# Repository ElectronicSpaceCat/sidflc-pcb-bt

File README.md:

# sidflc-pcb-bt

The primary pcb has the bluetooth module (where the firmware resides).

KiCad version: 7.0

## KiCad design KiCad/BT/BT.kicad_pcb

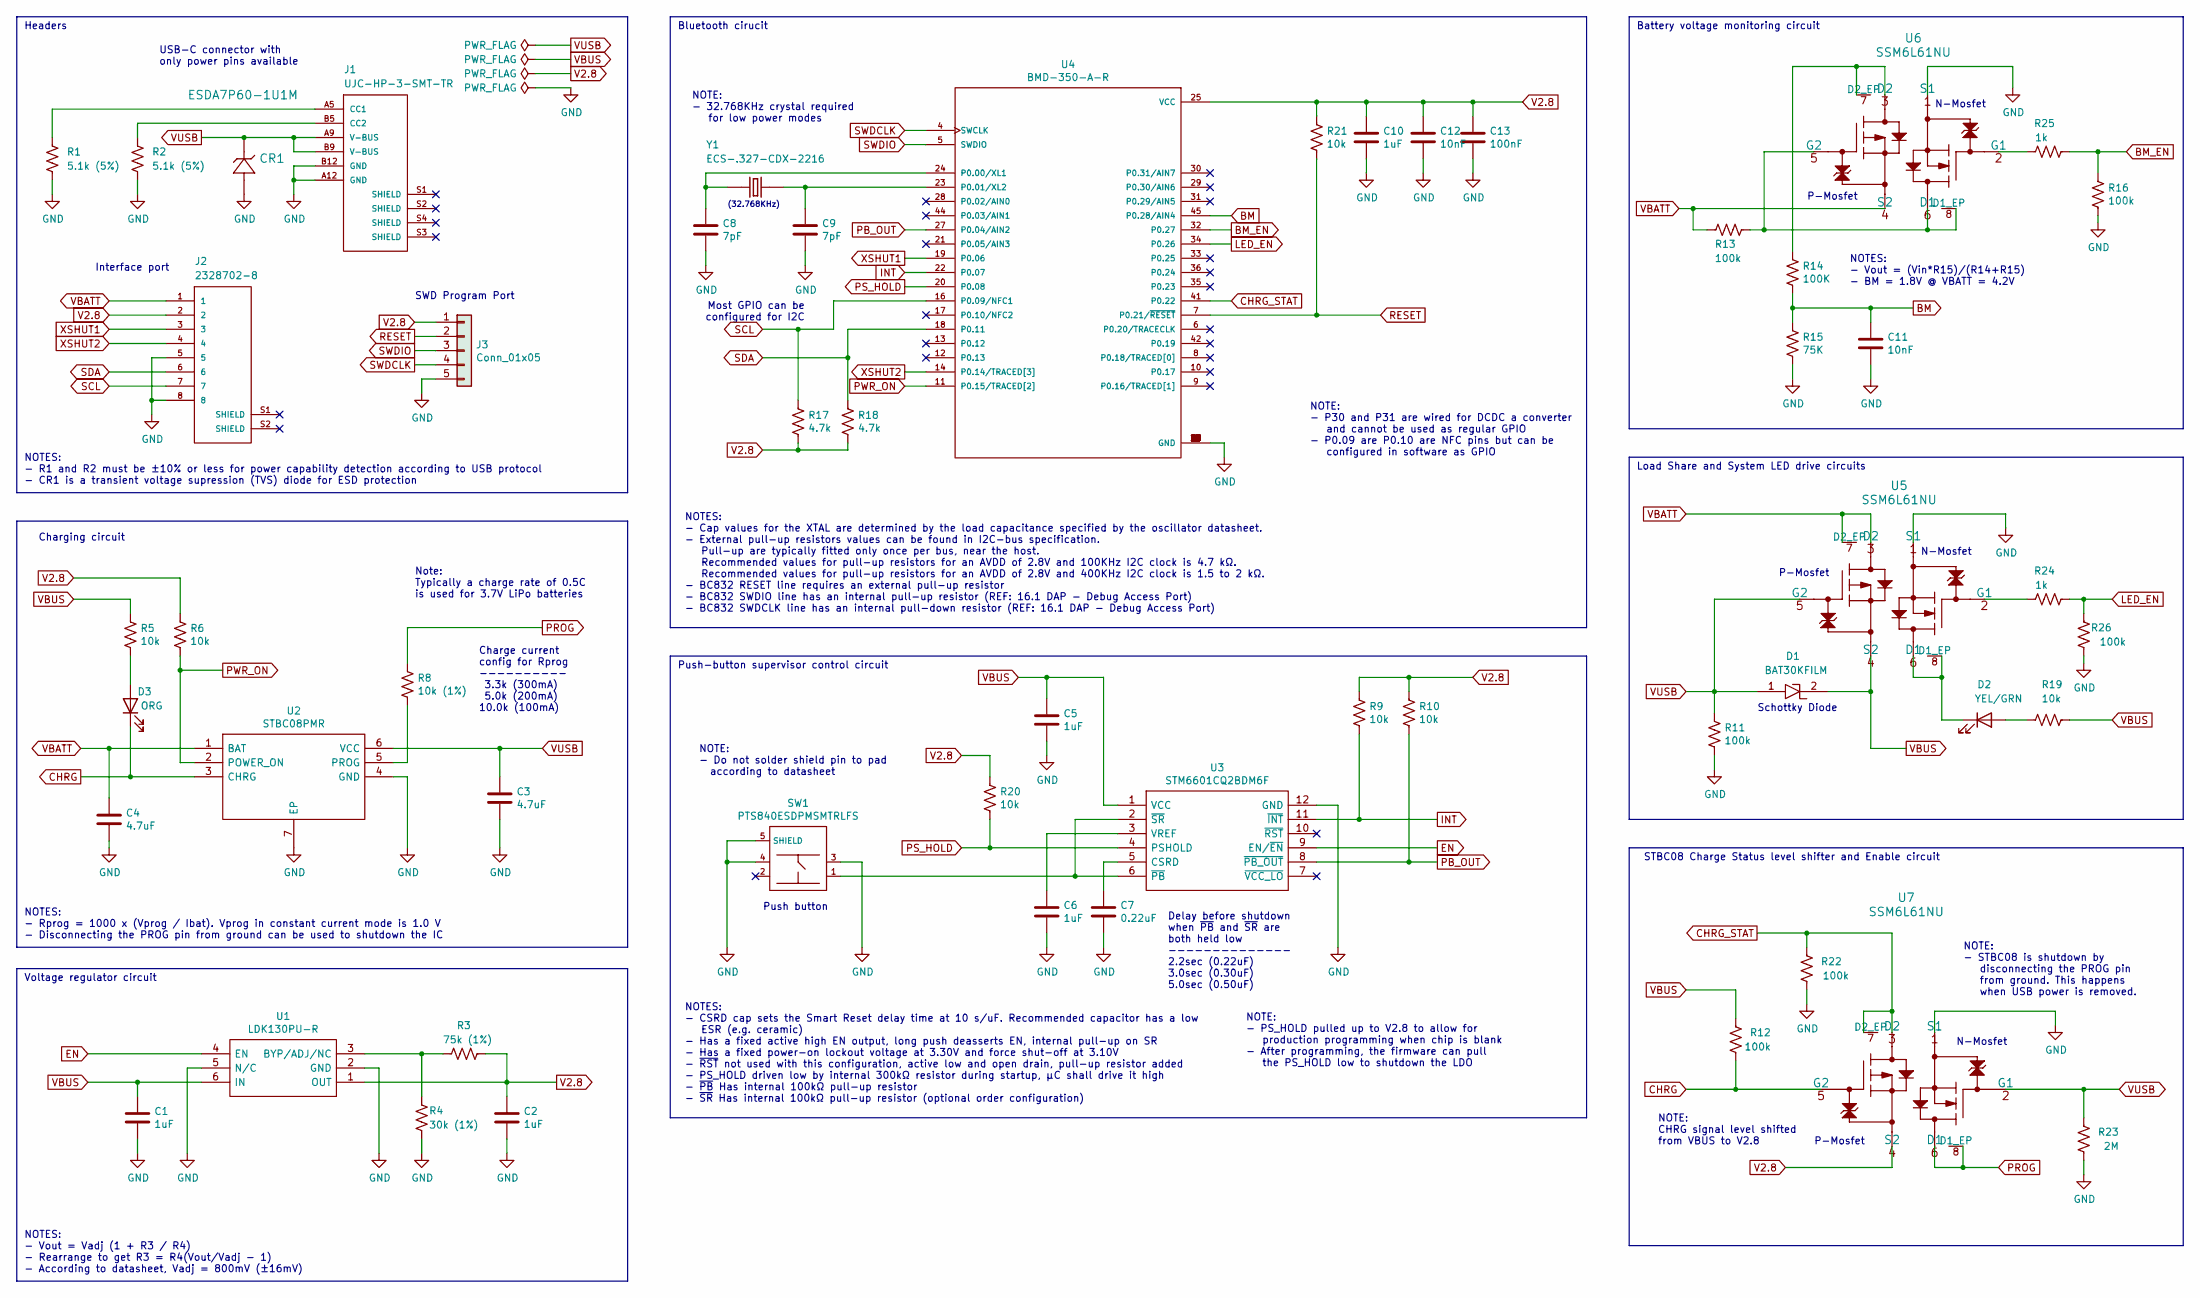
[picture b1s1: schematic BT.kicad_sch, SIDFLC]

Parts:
C1, C2, C5, C6, C10: 1uF; Capacitor_Taiyo_Yuden_0402
C3, C4: 4.7uF; Capacitor_Taiyo_Yuden_0402
C7: 0.22uF; Capacitor_Taiyo_Yuden_0402
C8, C9: 7pF; C_0201_0603Metric
C11, C12: 10nF; Capacitor_Taiyo_Yuden_0402
C13: 100nF; Capacitor_Taiyo_Yuden_0402
CR1: ESDA7P60-1U1M; ESDA7P601U1M
D1: BAT30KFILM; Manufacturer_Part_Number BAT30KFILM; Mouser Part Number 511-BAT30KFILM
D2: YEL/GRN; LED_QBLP595
D3: ORG; LED_QBLP595
J1: UJC-HP-3-SMT-TR; CUI_UJC-HP-3-SMT-TR; PARTREV 1.0
J2: 2328702-8; TE_2328702-8
J3: Conn_01x05; PinHeader_1x05_P1.00mm_Vertical
R1, R2: 5.1k (5%); Stackpole_Res_0402
R3: 75k (1%); Stackpole_Res_0402
R4: 30k (1%); Stackpole_Res_0402
R5, R6, R9, R10, R19, R20, R21: 10k; Stackpole_Res_0402
R8: 10k (1%); Stackpole_Res_0402
R11, R12, R13, R16, R22, R26: 100k; Stackpole_Res_0402
R14: 100K; Stackpole_Res_0402
R15: 75K; Stackpole_Res_0402
R17, R18: 4.7k; Stackpole_Res_0402
R23: 2M; Stackpole_Res_0402
R24, R25: 1k; Stackpole_Res_0402
SW1: PTS840ESDPMSMTRLFS
U1: LDK130PU-R; QFN40P120X130X45-6N; Manufacturer_Part_Number LDK120PU29R
U2: STBC08PMR; SON95P300X300X100-7N-D; Manufacturer_Part_Number STBC08PMR; Mouser Part Number 511-STBC08PMR
U3: STM6601CQ2BDM6F; STM6601AQ2BDM6F; Manufacturer_Part_Number STM6601CQ2BDM6F; Mouser Part Number 511-STM6601CQ2BDM6F
U4: BMD-350-A-R; XCVR_BMD-350-A-R; PARTREV 2.0
U5, U6, U7: SSM6L61NU; UDFN6
Y1: ECS-.327-CDX-2216; XTAL_ECS-.327-CDX-2216; PARTREV 2016

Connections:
BM: C11.1, R14.2, R15.1, U4.45 (P0.28/AIN4)
BM_EN: R16.1, R25.2, U4.32 (P0.27)
CHRG: D3.1 (K), R12.1, U2.3 (CHRG), U7.5 (G2)
CHRG_STAT: R22.2, U4.41 (P0.22), U7.3 (D2), U7.7 (D2_EP)
EN: U1.4 (EN), U3.9 (EN/~EN)
GND: C1.2, C2.2, C3.2, C4.2, C5.2, C6.2, C7.2, C8.2, C9.2, C10.2, C11.2, C12.2, C13.2, CR1.2, J1.A12 (GND), J1.B12 (GND), J2.5, J2.8, J3.5, R1.2, R2.2, R4.2, R11.2, R15.2, R16.2, R22.1, R23.1, R26.1, SW1.3, SW1.4, SW1.5 (SHIELD), U1.2 (GND), U1.5 (N/C), U2.4 (GND), U2.7 (EP), U3.12 (GND), U4.1 (GND), U4.2 (GND), U4.3 (GND), U4.15 (GND), U4.26 (GND), U4.37 (GND), U4.38 (GND), U4.39 (GND), U4.40 (GND), U4.43 (GND), U4.46 (GND), U4.47 (GND), U5.1 (S1), U6.1 (S1), U7.1 (S1)
INT: R9.2, U3.11 (~INT), U4.22 (P0.07)
LED_EN: R24.2, R26.2, U4.34 (P0.26)
unnamed: D2.2 (A), R19.2
unnamed: D2.1 (K), U5.6 (D1), U5.8 (D1_EP)
unnamed: D3.2 (A), R5.2
unnamed: J1.A5 (CC1), R1.1
unnamed: J1.B5 (CC2), R2.1
unnamed: R3.1, R4.1, U1.3 (BYP/ADJ/NC)
unnamed: R8.2, U2.5 (PROG)
unnamed: C7.1, U3.5 (CSRD)
unnamed: C6.1, U3.3 (VREF)
unnamed: SW1.1, U3.2 (~SR), U3.6 (~PB)
unnamed: C8.1, U4.24 (P0.00/XL1), Y1.1
unnamed: C9.1, U4.23 (P0.01/XL2), Y1.2
unnamed: R24.1, U5.2 (G1)
unnamed: R13.1, U6.5 (G2), U6.6 (D1), U6.8 (D1_EP)
unnamed: R14.1, U6.3 (D2), U6.7 (D2_EP)
unnamed: R25.1, U6.2 (G1)
PB_OUT: R10.2, U3.8 (~PB_OUT), U4.27 (P0.04/AIN2)
PROG: R8.1, U7.6 (D1), U7.8 (D1_EP)
PS_HOLD: R20.2, U3.4 (PSHOLD), U4.20 (P0.08)
PWR_ON: R6.2, U2.2 (POWER_ON), U4.11 (P0.15/TRACED[2])
RESET: J3.2, R21.2, U4.7 (P0.21/~RESET)
SCL: J2.7, R17.1, U4.16 (P0.09/NFC1)
SDA: J2.6, R18.1, U4.18 (P0.11)
SWDCLK: J3.4, U4.4 (SWCLK)
SWDIO: J3.3, U4.5 (SWDIO)
V2.8: C2.1, C10.1, C12.1, C13.1, J2.2, J3.1, R3.2, R6.1, R9.1, R10.1, R17.2, R18.2, R20.1, R21.1, U1.1 (OUT), U4.25 (VCC), U7.4 (S2)
VBATT: C4.1, J2.1, R13.2, U2.1 (BAT), U5.3 (D2), U5.7 (D2_EP), U6.4 (S2)
VBUS: C1.1, C5.1, D1.2, R5.1, R12.2, R19.1, U1.6 (IN), U3.1 (VCC), U5.4 (S2)
VUSB: C3.1, CR1.1, D1.1, J1.A9 (V-BUS), J1.B9 (V-BUS), R11.1, R23.2, U2.6 (VCC), U5.5 (G2), U7.2 (G1)
XSHUT1: J2.3, U4.19 (P0.06)
XSHUT2: J2.4, U4.14 (P0.14/TRACED[3])

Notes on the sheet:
SWD Program Port
Charge current config for Rprog ---------- 3.3k (300mA) 5.0k (200mA) 10.0k (100mA)
Push button
STBC08 Charge Status level shifter and Enable circuit
NOTES: - Cap values for the XTAL are determined by the load capacitance specified by the oscillator datasheet. - External pull-up resistors values can be found in I2C-bus specification. Pull-up are typically fitted only once per bus, near the host. Recommended values for pull-up resistors for an AV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
Headers
NOTE: - PS_HOLD pulled up to V2.8 to allow for production programming when chip is blank - After programming, the firmware can pull the PS_HOLD low to shutdown the LDO
NOTES: - R1 and R2 must be ±10% or less for power capability detection according to USB protocol - CR1 is a transient voltage supression (TVS) diode for ESD protection
N-Mosfet
(32.768KHz)
Voltage regulator circuit
Schottky Diode
NOTES: - Vout = Vadj (1 + R3 / R4) - Rearrange to get R3 = R4(Vout/Vadj - 1) - According to datasheet, Vadj = 800mV (±16mV)
Bluetooth cirucit
Note: Typically a charge rate of 0.5C is used for 3.7V LiPo batteries
NOTE: - Do not solder shield pin to pad according to datasheet
Interface port
Load Share and System LED drive circuits
Battery voltage monitoring circuit
NOTE: CHRG signal level shifted from VBUS to V2.8
NOTES: - Vout = (Vin*R15)/(R14+R15) - BM = 1.8V @ VBATT = 4.2V
Push-button supervisor control circuit
NOTE: - STBC08 is shutdown by disconnecting the PROG pin from ground. This happens when USB power is removed.
NOTE: - 32.768KHz crystal required for low power modes
Most GPIO can be configured for I2C
NOTES: - CSRD cap sets the Smart Reset delay time at 10 s/uF. Recommended capacitor has a low ESR (e.g. ceramic) - Has a fixed active high EN output, long push deasserts EN, internal pull-up on SR - Has a fixed power-on lockout voltage at 3.30V and force shut-off at 3.10V - ~{RST} not used with thi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
P-Mosfet
Charging circuit
Delay before shutdown when ~{PB} and ~{SR} are both held low -------------- 2.2sec (0.22uF) 3.0sec (0.30uF) 5.0sec (0.50uF)
NOTE: - P30 and P31 are wired for DCDC a converter and cannot be used as regular GPIO - P0.09 are P0.10 are NFC pins but can be configured in software as GPIO
NOTES: - Rprog = 1000 x (Vprog / Ibat). Vprog in constant current mode is 1.0 V - Disconnecting the PROG pin from ground can be used to shutdown the IC
USB-C connector with only power pins available

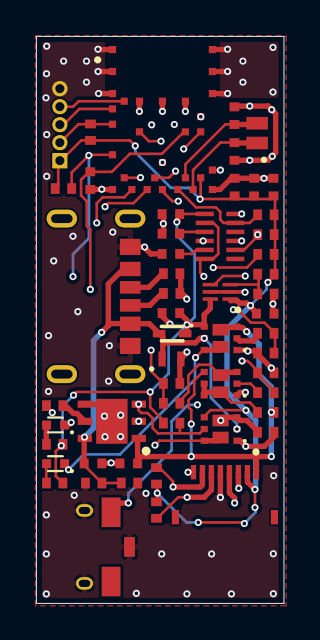
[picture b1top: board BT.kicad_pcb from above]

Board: 4 copper layers, 13.8 x 31.5 mm, 54 parts (0 on the bottom side), 39 nets.

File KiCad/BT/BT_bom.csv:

"#","Reference","Qty","Value","Footprint","DNP"
"1","C1, C2, C5, C6, C10","5","1uF","Capacitor_Taiyo_Yuden_0402:Capacitor_Taiyo_Yuden_0402",""
"2","C3, C4","2","4.7uF","Capacitor_Taiyo_Yuden_0402:Capacitor_Taiyo_Yuden_0402",""
"3","C7","1","0.22uF","Capacitor_Taiyo_Yuden_0402:Capacitor_Taiyo_Yuden_0402",""
"4","C8, C9","2","7pF","Capacitor_SMD:C_0201_0603Metric",""
"5","C11, C12","2","10nF","Capacitor_Taiyo_Yuden_0402:Capacitor_Taiyo_Yuden_0402",""
"6","C13","1","100nF","Capacitor_Taiyo_Yuden_0402:Capacitor_Taiyo_Yuden_0402",""
"7","CR1","1","ESDA7P60-1U1M","ESDA7P601U1M:ESDA7P601U1M",""
"8","D1","1","BAT30KFILM","BAT30KFILM:BAT30KFILM",""
"9","D2","1","YEL/GRN","LED_QBLP595:LED_QBLP595",""
"10","D3","1","ORG","LED_QBLP595:LED_QBLP595",""
"11","J1","1","UJC-HP-3-SMT-TR","CUI_UJC-HP-3-SMT-TR",""
"12","J2","1","2328702-8","2328702-8:TE_2328702-8",""
"13","J3","1","Conn_01x05","Connector_PinHeader_1.00mm:PinHeader_1x05_P1.00mm_Vertical",""
"14","R1, R2","2","5.1k (5%)","Stackpole_Res_0402:Stackpole_Res_0402",""
"15","R3","1","75k (1%)","Stackpole_Res_0402:Stackpole_Res_0402",""
"16","R4","1","30k (1%)","Stackpole_Res_0402:Stackpole_Res_0402",""
"17","R5, R6, R9, R10, R19, R20, R21","7","10k","Stackpole_Res_0402:Stackpole_Res_0402",""
"18","R8","1","10k (1%)","Stackpole_Res_0402:Stackpole_Res_0402",""
"19","R11, R12, R13, R16, R22, R26","6","100k","Stackpole_Res_0402:Stackpole_Res_0402",""
"20","R14","1","4M","Stackpole_Res_0402:Stackpole_Res_0402",""
"21","R15","1","3M","Stackpole_Res_0402:Stackpole_Res_0402",""
"22","R17, R18","2","4.7k","Stackpole_Res_0402:Stackpole_Res_0402",""
"23","R23","1","2M","Stackpole_Res_0402:Stackpole_Res_0402",""
"24","R24, R25","2","1k","Stackpole_Res_0402:Stackpole_Res_0402",""
"25","SW1","1","PTS840ESDPMSMTRLFS","PTS840ESDPMSMTRLFS:PTS840ESDPMSMTRLFS",""
"26","U1","1","LDK130PU-R","QFN40P120X130X45-6N",""
"27","U2","1","STBC08PMR","STBC08PMR:SON95P300X300X100-7N-D",""
"28","U3","1","STM6601CQ2BDM6F","STM6601AQ2BDM6F:STM6601AQ2BDM6F",""
"29","U4","1","BMD-350-A-R","XCVR_BMD-350-A-R",""
"30","U5, U6, U7","3","SSM6L61NU","UDFN6",""
"31","Y1","1","ECS-.327-CDX-2216","ECS-.327-7-34R-TR:XTAL_ECS-.327-CDX-2216",""

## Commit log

2023-10-17 minor updates
2023-11-21 swapped SWDIO/SWCLK, BM pin moved to AN4
2023-12-09 updated sch rev and minor note edit
2024-05-09 updated schematic notes
2025-03-22 forgot what this update was about

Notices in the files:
parts and their libraries:
Copyright 2016 Accelerated Designs. All rights reserved.
